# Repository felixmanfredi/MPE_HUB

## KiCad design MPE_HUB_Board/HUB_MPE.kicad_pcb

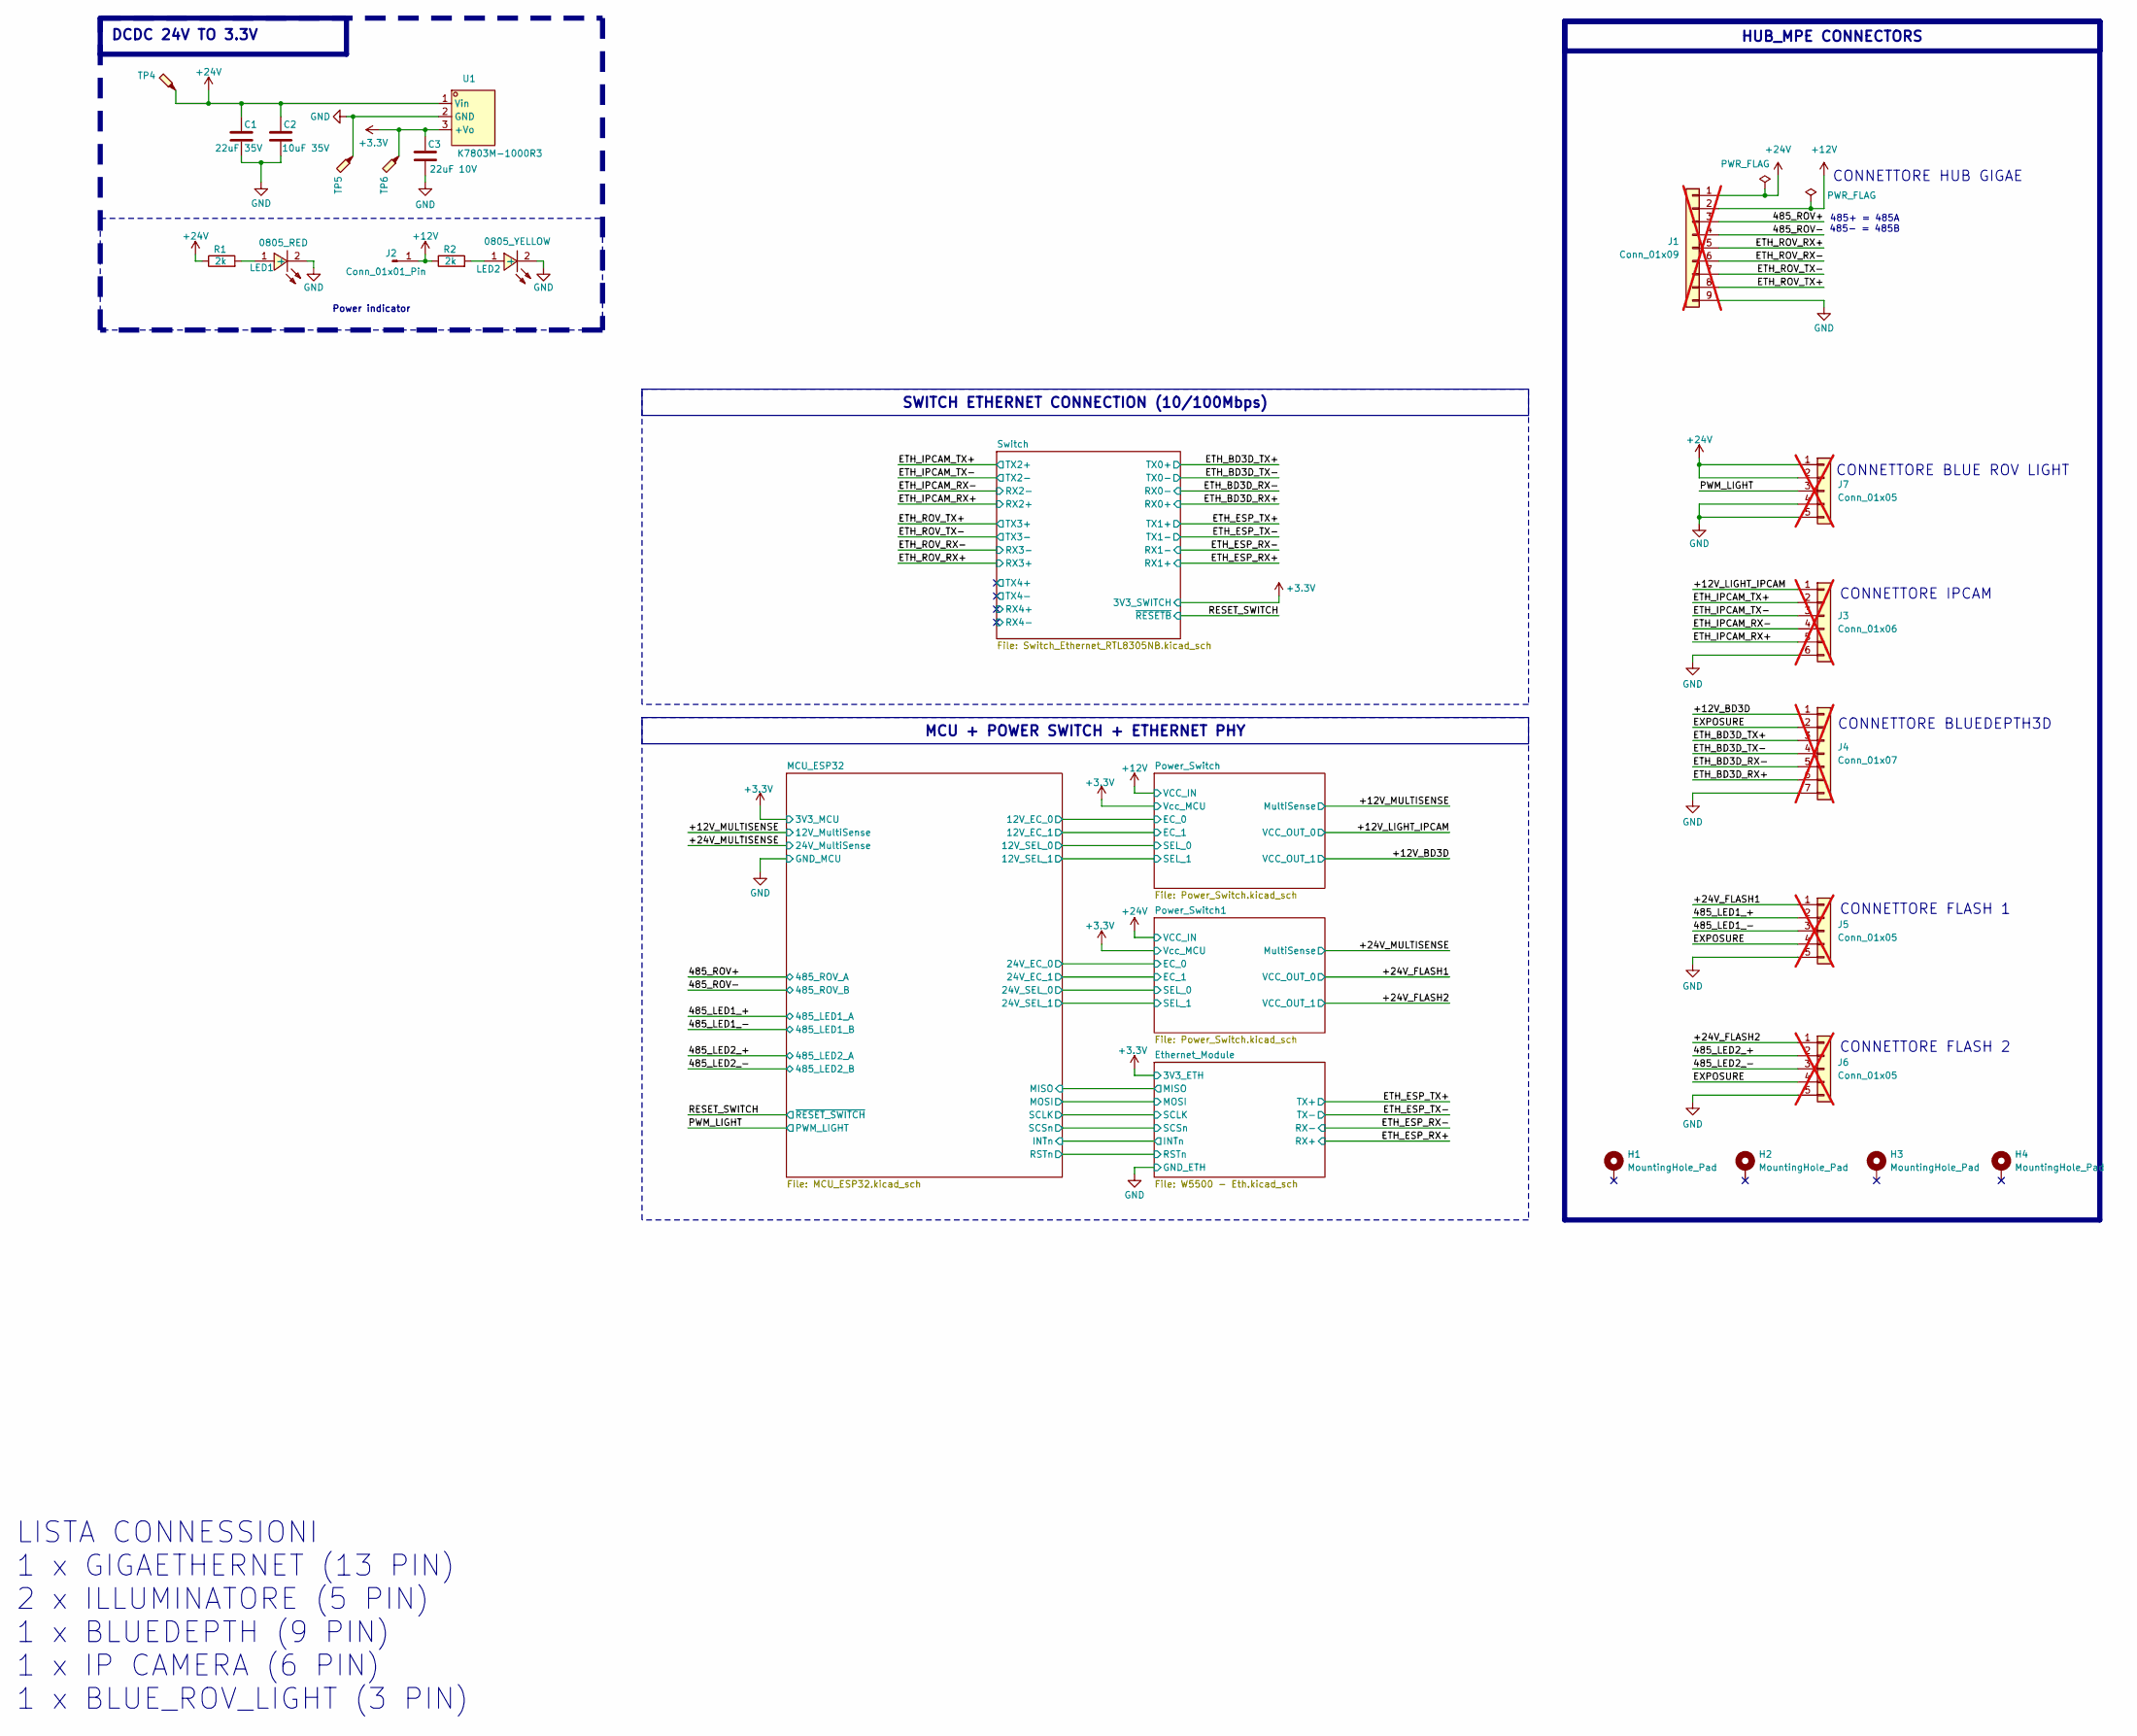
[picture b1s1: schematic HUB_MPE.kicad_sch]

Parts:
C1: 22uF 35V; C_1206_3216Metric; LCSC C342620
C2: 10uF 35V; C_0603_1608Metric; LCSC C194427
C3: 22uF 10V; C_0603_1608Metric; LCSC C60077
H1, H2, H3, H4: MountingHole_Pad; MountingHole_3.2mm_M3_Pad_Via
J1: Conn_01x09; JST_VH_B9P-VH-B_1x09_P3.96mm_Vertical; not fitted
J2: Conn_01x01_Pin; SolderWire-0.75sqmm_1x01_D1.25mm_OD3.5mm
J3: Conn_01x06; JST_VH_B6P-VH-B_1x06_P3.96mm_Vertical; not fitted
J4: Conn_01x07; JST_VH_B7P-VH-B_1x07_P3.96mm_Vertical; not fitted
J5, J6, J7: Conn_01x05; JST_VH_B5P-VH-B_1x05_P3.96mm_Vertical; not fitted
LED1: 0805_RED; LED0805-R-RD; LCSC Part C84256
LED2: 0805_YELLOW; LED0805-R-RD; LCSC Part C2296
R1, R2: 2k; R_0603_1608Metric; LCSC C22975
TP4, TP5, TP6: TestPoint_Probe; TEST-TH_BD2.54-P1.39; LCSC C238122
U1: K7803M-1000R3; PWRM-TH_DEXU_K78XXM-1000R3_XXXXXX; LCSC Part C2916516

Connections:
+3.3V: C3.1, TP6.1, U1.3 (+Vo); also elsewhere on the board
+12V: J1.2, J2.1, R2.1; also elsewhere on the board
+24V: C1.1, C2.1, J1.1, J7.1, J7.2, R1.1, TP4.1, U1.1 (Vin); also elsewhere on the board
/485_LED1_+: J5.2; also elsewhere on the board
/485_LED1_-: J5.3; also elsewhere on the board
/485_LED2_+: J6.2; also elsewhere on the board
/485_LED2_-: J6.3; also elsewhere on the board
/485_ROV+: J1.3; also elsewhere on the board
/485_ROV-: J1.4; also elsewhere on the board
/+12V_BD3D: J4.1; also elsewhere on the board
/+12V_LIGHT_IPCAM: J3.1; also elsewhere on the board
/+24V_FLASH1: J5.1; also elsewhere on the board
/+24V_FLASH2: J6.1; also elsewhere on the board
/ETH_BD3D_RX+: J4.6; also elsewhere on the board
/ETH_BD3D_RX-: J4.5; also elsewhere on the board
/ETH_BD3D_TX+: J4.3; also elsewhere on the board
/ETH_BD3D_TX-: J4.4; also elsewhere on the board
/ETH_IPCAM_RX+: J3.5; also elsewhere on the board
/ETH_IPCAM_RX-: J3.4; also elsewhere on the board
/ETH_IPCAM_TX+: J3.2; also elsewhere on the board
/ETH_IPCAM_TX-: J3.3; also elsewhere on the board
/ETH_ROV_RX+: J1.5; also elsewhere on the board
/ETH_ROV_RX-: J1.6; also elsewhere on the board
/ETH_ROV_TX+: J1.8; also elsewhere on the board
/ETH_ROV_TX-: J1.7; also elsewhere on the board
/EXPOSURE: J4.2, J5.4, J6.4
/PWM_LIGHT: J7.3; also elsewhere on the board
unnamed: LED1.1 (+), R1.2
unnamed: LED2.1 (+), R2.2

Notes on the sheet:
CONNETTORE FLASH 1
Power indicator
CONNETTORE HUB GIGAE
CONNETTORE IPCAM
485+ = 485A 485- = 485B
LISTA CONNESSIONI 1 x GIGAETHERNET (13 PIN) 2 x ILLUMINATORE (5 PIN) 1 x BLUEDEPTH (9 PIN) 1 x IP CAMERA (6 PIN) 1 x BLUE_ROV_LIGHT (3 PIN)
CONNETTORE BLUEDEPTH3D
CONNETTORE BLUE ROV LIGHT
CONNETTORE FLASH 2
MCU + POWER SWITCH + ETHERNET PHY
HUB_MPE CONNECTORS
SWITCH ETHERNET CONNECTION (10/100Mbps)
DCDC 24V TO 3.3V

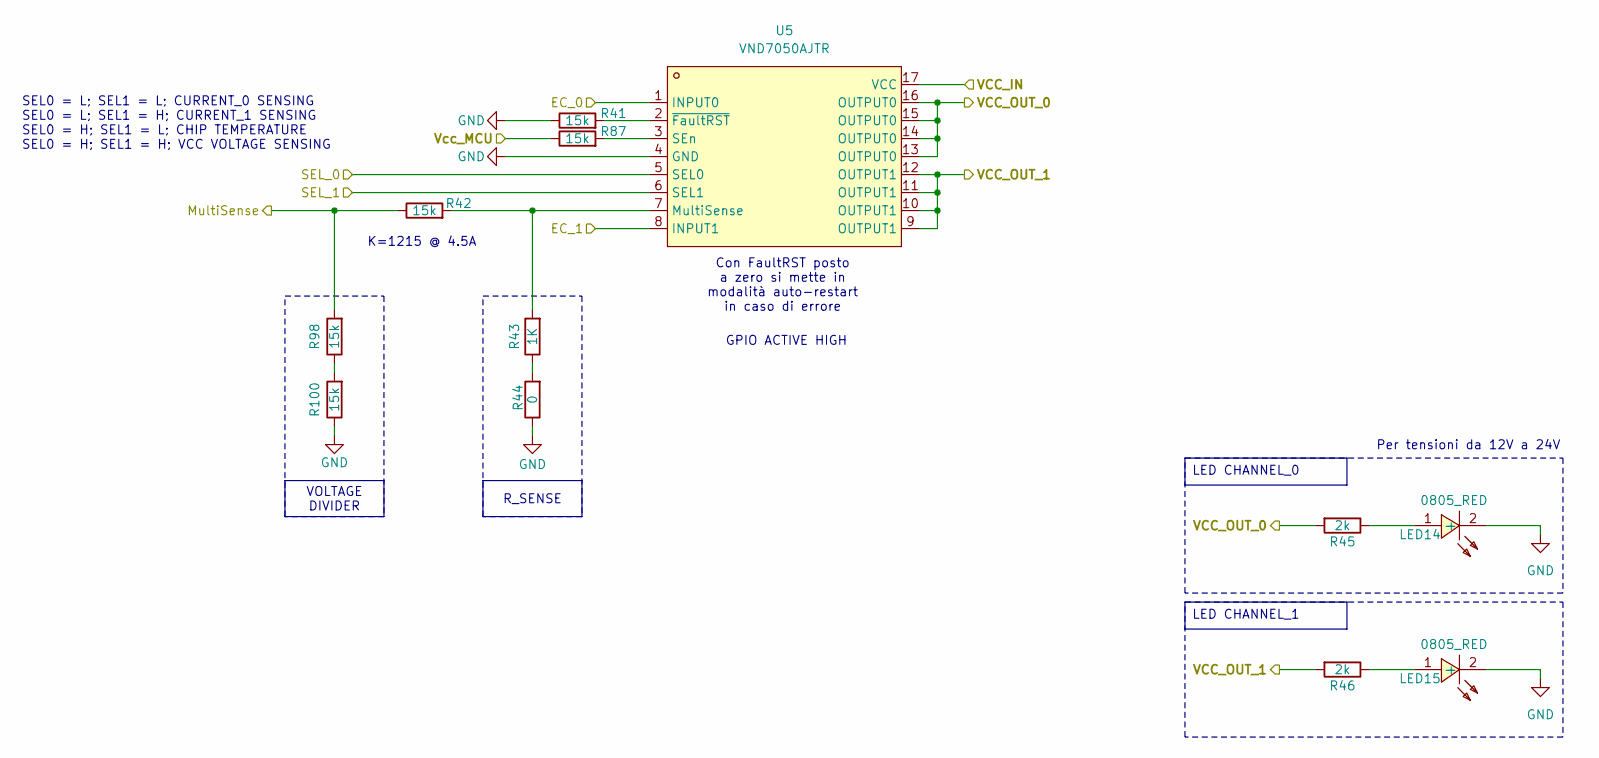
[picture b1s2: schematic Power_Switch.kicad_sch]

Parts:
LED14, LED15: 0805_RED; LED0805-R-RD; LCSC Part C84256
R41, R42, R87, R98, R100: 15k; R_0603_1608Metric; LCSC C22809
R43: 1K; R_0603_1608Metric; LCSC Part C21190
R44: 0; R_0603_1608Metric; LCSC C21189
R45, R46: 2k; R_0603_1608Metric; LCSC C22975
U5: VND7050AJTR; POWERSSO-16_L4.9-W3.9-P0.50-LS6.0-BL-EP; LCSC Part C443997

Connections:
+3.3V: R87.1; also elsewhere on the board
+12V: U5.17 (VCC); also elsewhere on the board
/+12V_BD3D: R46.2, U5.9 (OUTPUT1), U5.10 (OUTPUT1), U5.11 (OUTPUT1), U5.12 (OUTPUT1); also elsewhere on the board
/+12V_LIGHT_IPCAM: R45.2, U5.13 (OUTPUT0), U5.14 (OUTPUT0), U5.15 (OUTPUT0), U5.16 (OUTPUT0); also elsewhere on the board
/+12V_MULTISENSE: R42.1, R98.2; also elsewhere on the board
/MCU_ESP32/12V_EC_0: U5.1 (INPUT0); also elsewhere on the board
/MCU_ESP32/12V_EC_1: U5.8 (INPUT1); also elsewhere on the board
/MCU_ESP32/12V_SEL_0: U5.5 (SEL0); also elsewhere on the board
/MCU_ESP32/12V_SEL_1: U5.6 (SEL1); also elsewhere on the board
unnamed: LED14.1 (+), R45.1
unnamed: LED15.1 (+), R46.1
unnamed: R43.1, R44.2
unnamed: R98.1, R100.2
unnamed: R42.2, R43.2, U5.7 (MultiSense)
unnamed: R87.2, U5.3 (SEn)
unnamed: R41.2, U5.2 (~FaultRST)

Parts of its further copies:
LED16, LED17: 0805_RED; LED0805-R-RD; LCSC Part C84256
R47, R48, R88, R99, R101: 15k; R_0603_1608Metric; LCSC C22809
R49: 1K; R_0603_1608Metric; LCSC Part C21190
R50: 0; R_0603_1608Metric; LCSC C21189
R51, R52: 2k; R_0603_1608Metric; LCSC C22975
U6: VND7050AJTR; POWERSSO-16_L4.9-W3.9-P0.50-LS6.0-BL-EP; LCSC Part C443997

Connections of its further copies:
+3.3V: R88.1; also elsewhere on the board
+24V: U6.17 (VCC); also elsewhere on the board
/+24V_FLASH1: R51.2, U6.13 (OUTPUT0), U6.14 (OUTPUT0), U6.15 (OUTPUT0), U6.16 (OUTPUT0); also elsewhere on the board
/+24V_FLASH2: R52.2, U6.9 (OUTPUT1), U6.10 (OUTPUT1), U6.11 (OUTPUT1), U6.12 (OUTPUT1); also elsewhere on the board
/+24V_MULTISENSE: R48.1, R99.2; also elsewhere on the board
/MCU_ESP32/24V_EC_0: U6.1 (INPUT0); also elsewhere on the board
/MCU_ESP32/24V_EC_1: U6.8 (INPUT1); also elsewhere on the board
/MCU_ESP32/24V_SEL_0: U6.5 (SEL0); also elsewhere on the board
/MCU_ESP32/24V_SEL_1: U6.6 (SEL1); also elsewhere on the board
unnamed: LED16.1 (+), R51.1
unnamed: LED17.1 (+), R52.1
unnamed: R49.1, R50.2
unnamed: R99.1, R101.2
unnamed: R48.2, R49.2, U6.7 (MultiSense)
unnamed: R88.2, U6.3 (SEn)
unnamed: R47.2, U6.2 (~FaultRST)

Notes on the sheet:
K=1215 @ 4.5A
Per tensioni da 12V a 24V
GPIO ACTIVE HIGH
SEL0 = L; SEL1 = L; CURRENT_0 SENSING SEL0 = L; SEL1 = H; CURRENT_1 SENSING SEL0 = H; SEL1 = L; CHIP TEMPERATURE SEL0 = H; SEL1 = H; VCC VOLTAGE SENSING
Con FaultRST posto a zero si mette in modalità auto-restart in caso di errore
R_SENSE
VOLTAGE DIVIDER
LED CHANNEL_1
LED CHANNEL_0

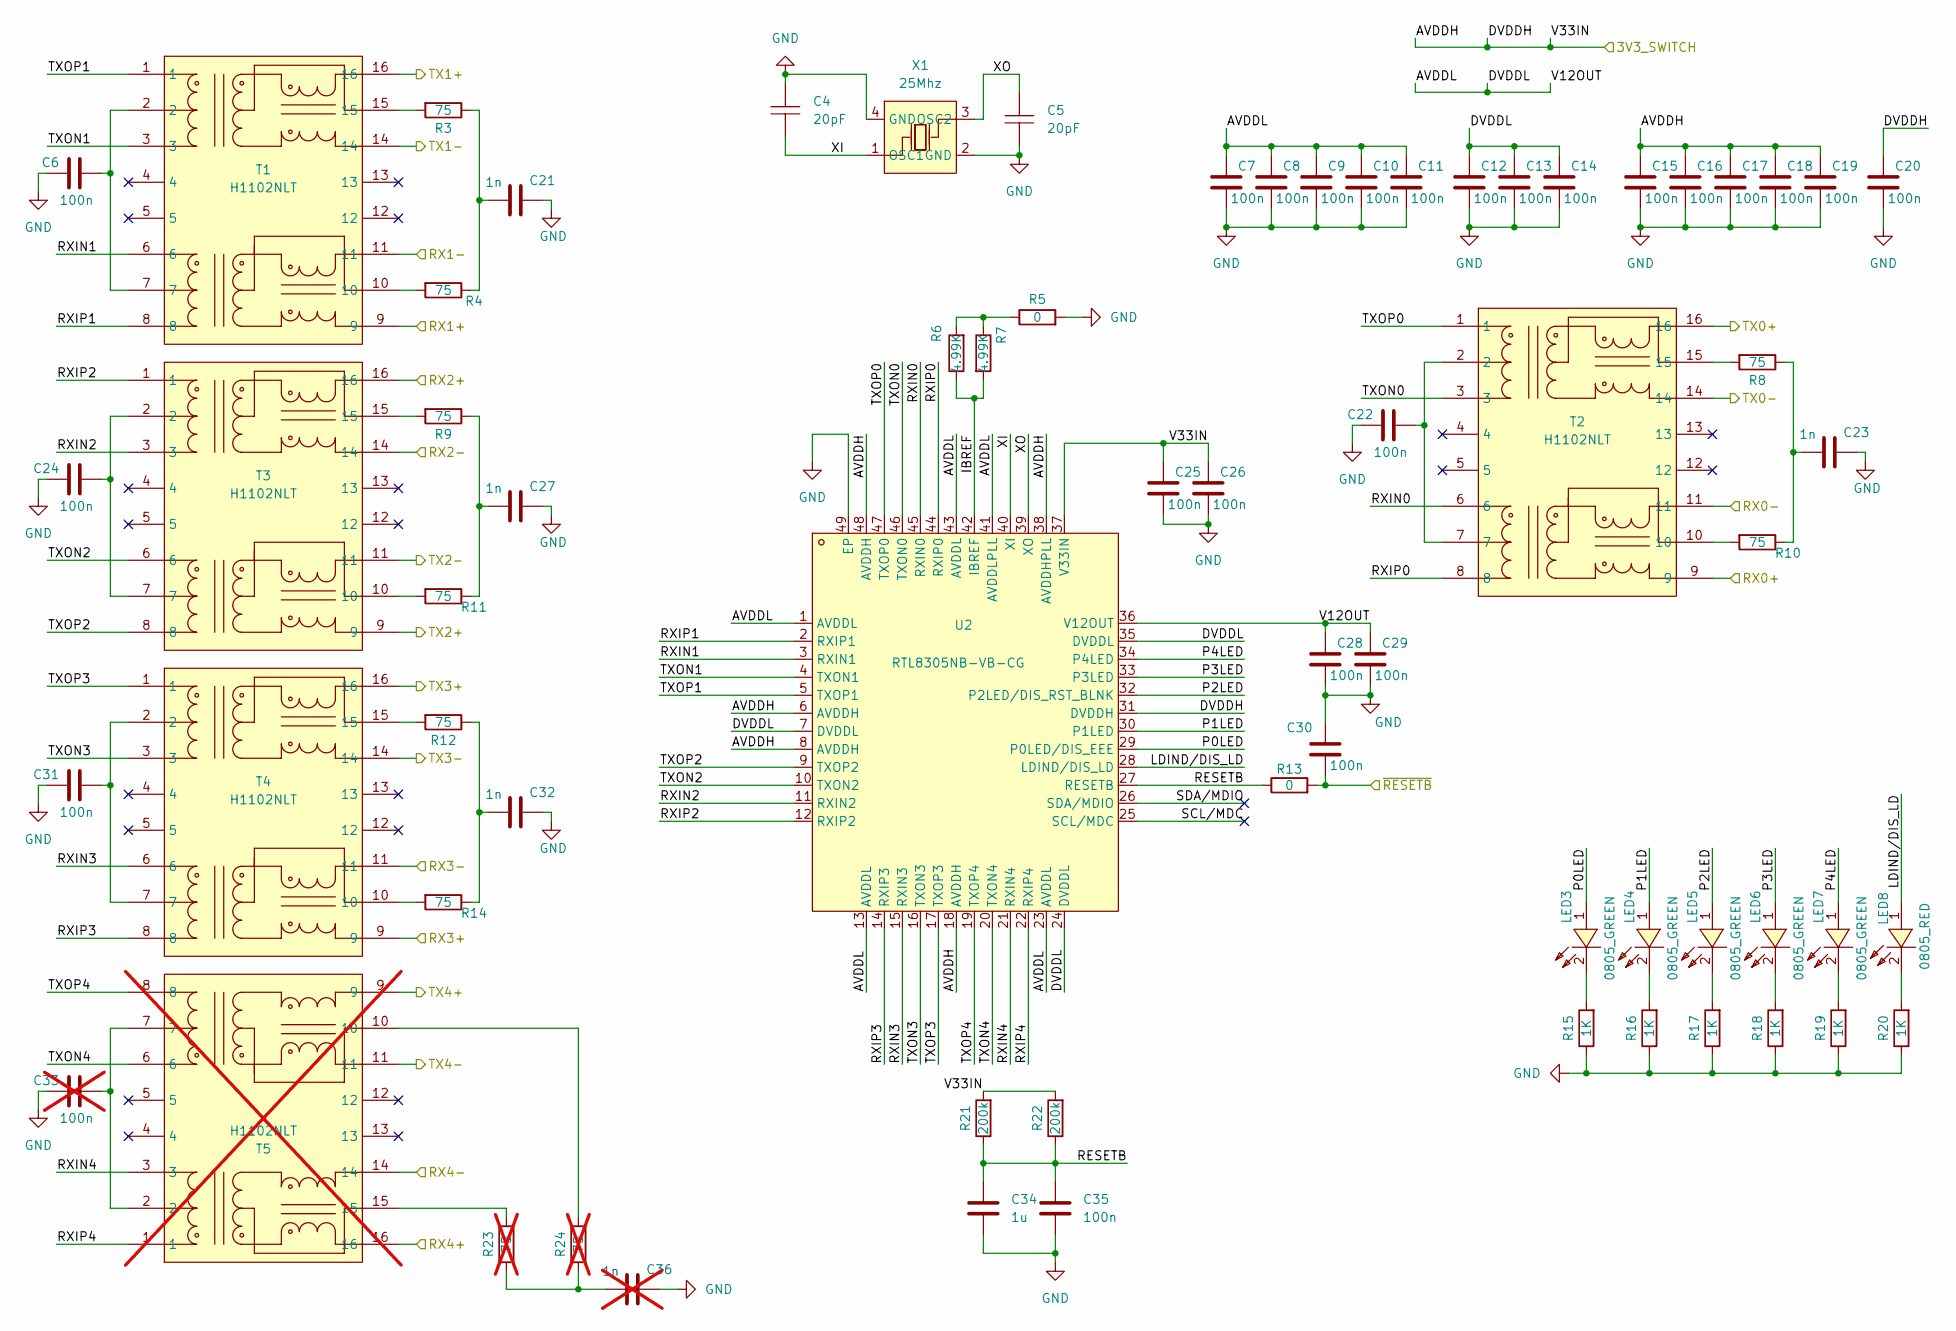
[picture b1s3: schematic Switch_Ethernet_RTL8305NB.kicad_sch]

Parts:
C4, C5: 20pF; C_0603_1608Metric; LCSC Part C1648
C6, C7, C8, C9, C10, C11, C12, C13, C14, C15, C16, C17, C18, C19, C20, C22, C24, C25, C26, C28, C29, C30, C31, C35: 100n; C_0603_1608Metric; LCSC Part C14663
C21, C23, C27, C32: 1n; C_0603_1608Metric; LCSC Part C1588
C33: 100n; C_0603_1608Metric; LCSC Part C14663; not fitted
C34: 1u; C_0603_1608Metric; LCSC Part C15849
C36: 1n; C_0603_1608Metric; LCSC Part C1588; not fitted
LED3, LED4, LED5, LED6, LED7: 0805_GREEN; LED0805-R-RD; LCSC Part C2297
LED8: 0805_RED; LED0805-R-RD; LCSC Part C84256
R3, R4, R8, R9, R10, R11, R12, R14: 75; R_0603_1608Metric; LCSC Part C4275
R5, R13: 0; R_0603_1608Metric; LCSC Part C21189
R6, R7: 4.99K; R_0603_1608Metric; LCSC Part C23046
R15, R16, R17, R18, R19, R20: 1K; R_0603_1608Metric; LCSC Part C21190
R21, R22: 200k; R_0603_1608Metric; LCSC Part C25811
R23, R24: 75; R_0603_1608Metric; LCSC Part C4275; not fitted
T1, T2, T3, T4: H1102NLT; XFMR-SMD_H1102NLT; LCSC Part C18584
T5: H1102NLT; XFMR-SMD_H1102NLT; LCSC Part C18584; not fitted
U2: RTL8305NB-VB-CG; QFN-48_L6.0-W6.0-P0.40-TL-EP4.4; LCSC Part C3010343
X1: 25Mhz; CRYSTAL-SMD_4P-L3.2-W2.5-BL; LCSC Part C9006

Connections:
+3.3V: C15.1, C16.1, C17.1, C18.1, C19.1, C20.1, C25.1, C26.1, R21.2, R22.2, U2.6 (AVDDH), U2.8 (AVDDH), U2.18 (AVDDH), U2.31 (DVDDH), U2.37 (V33IN), U2.38 (AVDDHPLL), U2.48 (AVDDH); also elsewhere on the board
/ETH_BD3D_RX+: T2.9; also elsewhere on the board
/ETH_BD3D_RX-: T2.11; also elsewhere on the board
/ETH_BD3D_TX+: T2.16; also elsewhere on the board
/ETH_BD3D_TX-: T2.14; also elsewhere on the board
/ETH_ESP_RX+: T1.9; also elsewhere on the board
/ETH_ESP_RX-: T1.11; also elsewhere on the board
/ETH_ESP_TX+: T1.16; also elsewhere on the board
/ETH_ESP_TX-: T1.14; also elsewhere on the board
/ETH_IPCAM_RX+: T3.16; also elsewhere on the board
/ETH_IPCAM_RX-: T3.14; also elsewhere on the board
/ETH_IPCAM_TX+: T3.9; also elsewhere on the board
/ETH_IPCAM_TX-: T3.11; also elsewhere on the board
/ETH_ROV_RX+: T4.9; also elsewhere on the board
/ETH_ROV_RX-: T4.11; also elsewhere on the board
/ETH_ROV_TX+: T4.16; also elsewhere on the board
/ETH_ROV_TX-: T4.14; also elsewhere on the board
/RESET_SWITCH: C30.2, R13.2; also elsewhere on the board
/Switch/LDIND/DIS_LD: LED8.1 (+), U2.28 (LDIND/DIS_LD)
/Switch/P0LED: LED3.1 (A), U2.29 (P0LED/DIS_EEE)
/Switch/P1LED: LED4.1 (A), U2.30 (P1LED)
/Switch/P2LED: LED5.1 (A), U2.32 (P2LED/DIS_RST_BLNK)
/Switch/P3LED: LED6.1 (A), U2.33 (P3LED)
/Switch/P4LED: LED7.1 (A), U2.34 (P4LED)
/Switch/RESETB: C34.1, C35.1, R13.1, R21.1, R22.1, U2.27 (RESETB)
/Switch/RXIN0: T2.6, U2.45 (RXIN0)
/Switch/RXIN1: T1.6, U2.3 (RXIN1)
/Switch/RXIN2: T3.3, U2.11 (RXIN2)
/Switch/RXIP0: T2.8, U2.44 (RXIP0)
/Switch/RXIP1: T1.8, U2.2 (RXIP1)
/Switch/RXIP2: T3.1, U2.12 (RXIP2)
/Switch/SCL/MDC: U2.25 (SCL/MDC)
/Switch/SDA/MDIO: U2.26 (SDA/MDIO)
/Switch/TXON0: T2.3, U2.46 (TXON0)
/Switch/TXON1: T1.3, U2.4 (TXON1)
/Switch/TXON2: T3.6, U2.10 (TXON2)
/Switch/TXOP0: T2.1, U2.47 (TXOP0)
/Switch/TXOP1: T1.1, U2.5 (TXOP1)
/Switch/TXOP2: T3.8, U2.9 (TXOP2)
/Switch/XI: C4.1, U2.40 (XI), X1.1 (OSC1)
unnamed: C6.1, T1.2, T1.7
unnamed: C21.2, R3.1, R4.1
unnamed: C22.1, T2.2, T2.7
unnamed: C24.1, T3.2, T3.7
unnamed: C27.2, R9.1, R11.1
unnamed: C32.2, R12.1, R14.1
unnamed: LED3.2 (K), R15.2
unnamed: LED4.2 (K), R16.2
unnamed: LED5.2 (K), R17.2
unnamed: LED6.2 (K), R18.2
unnamed: LED7.2 (K), R19.2
unnamed: LED8.2 (-), R20.2
unnamed: R3.2, T1.15
unnamed: R4.2, T1.10
unnamed: R8.2, T2.15
unnamed: R9.2, T3.15
unnamed: R11.2, T3.10

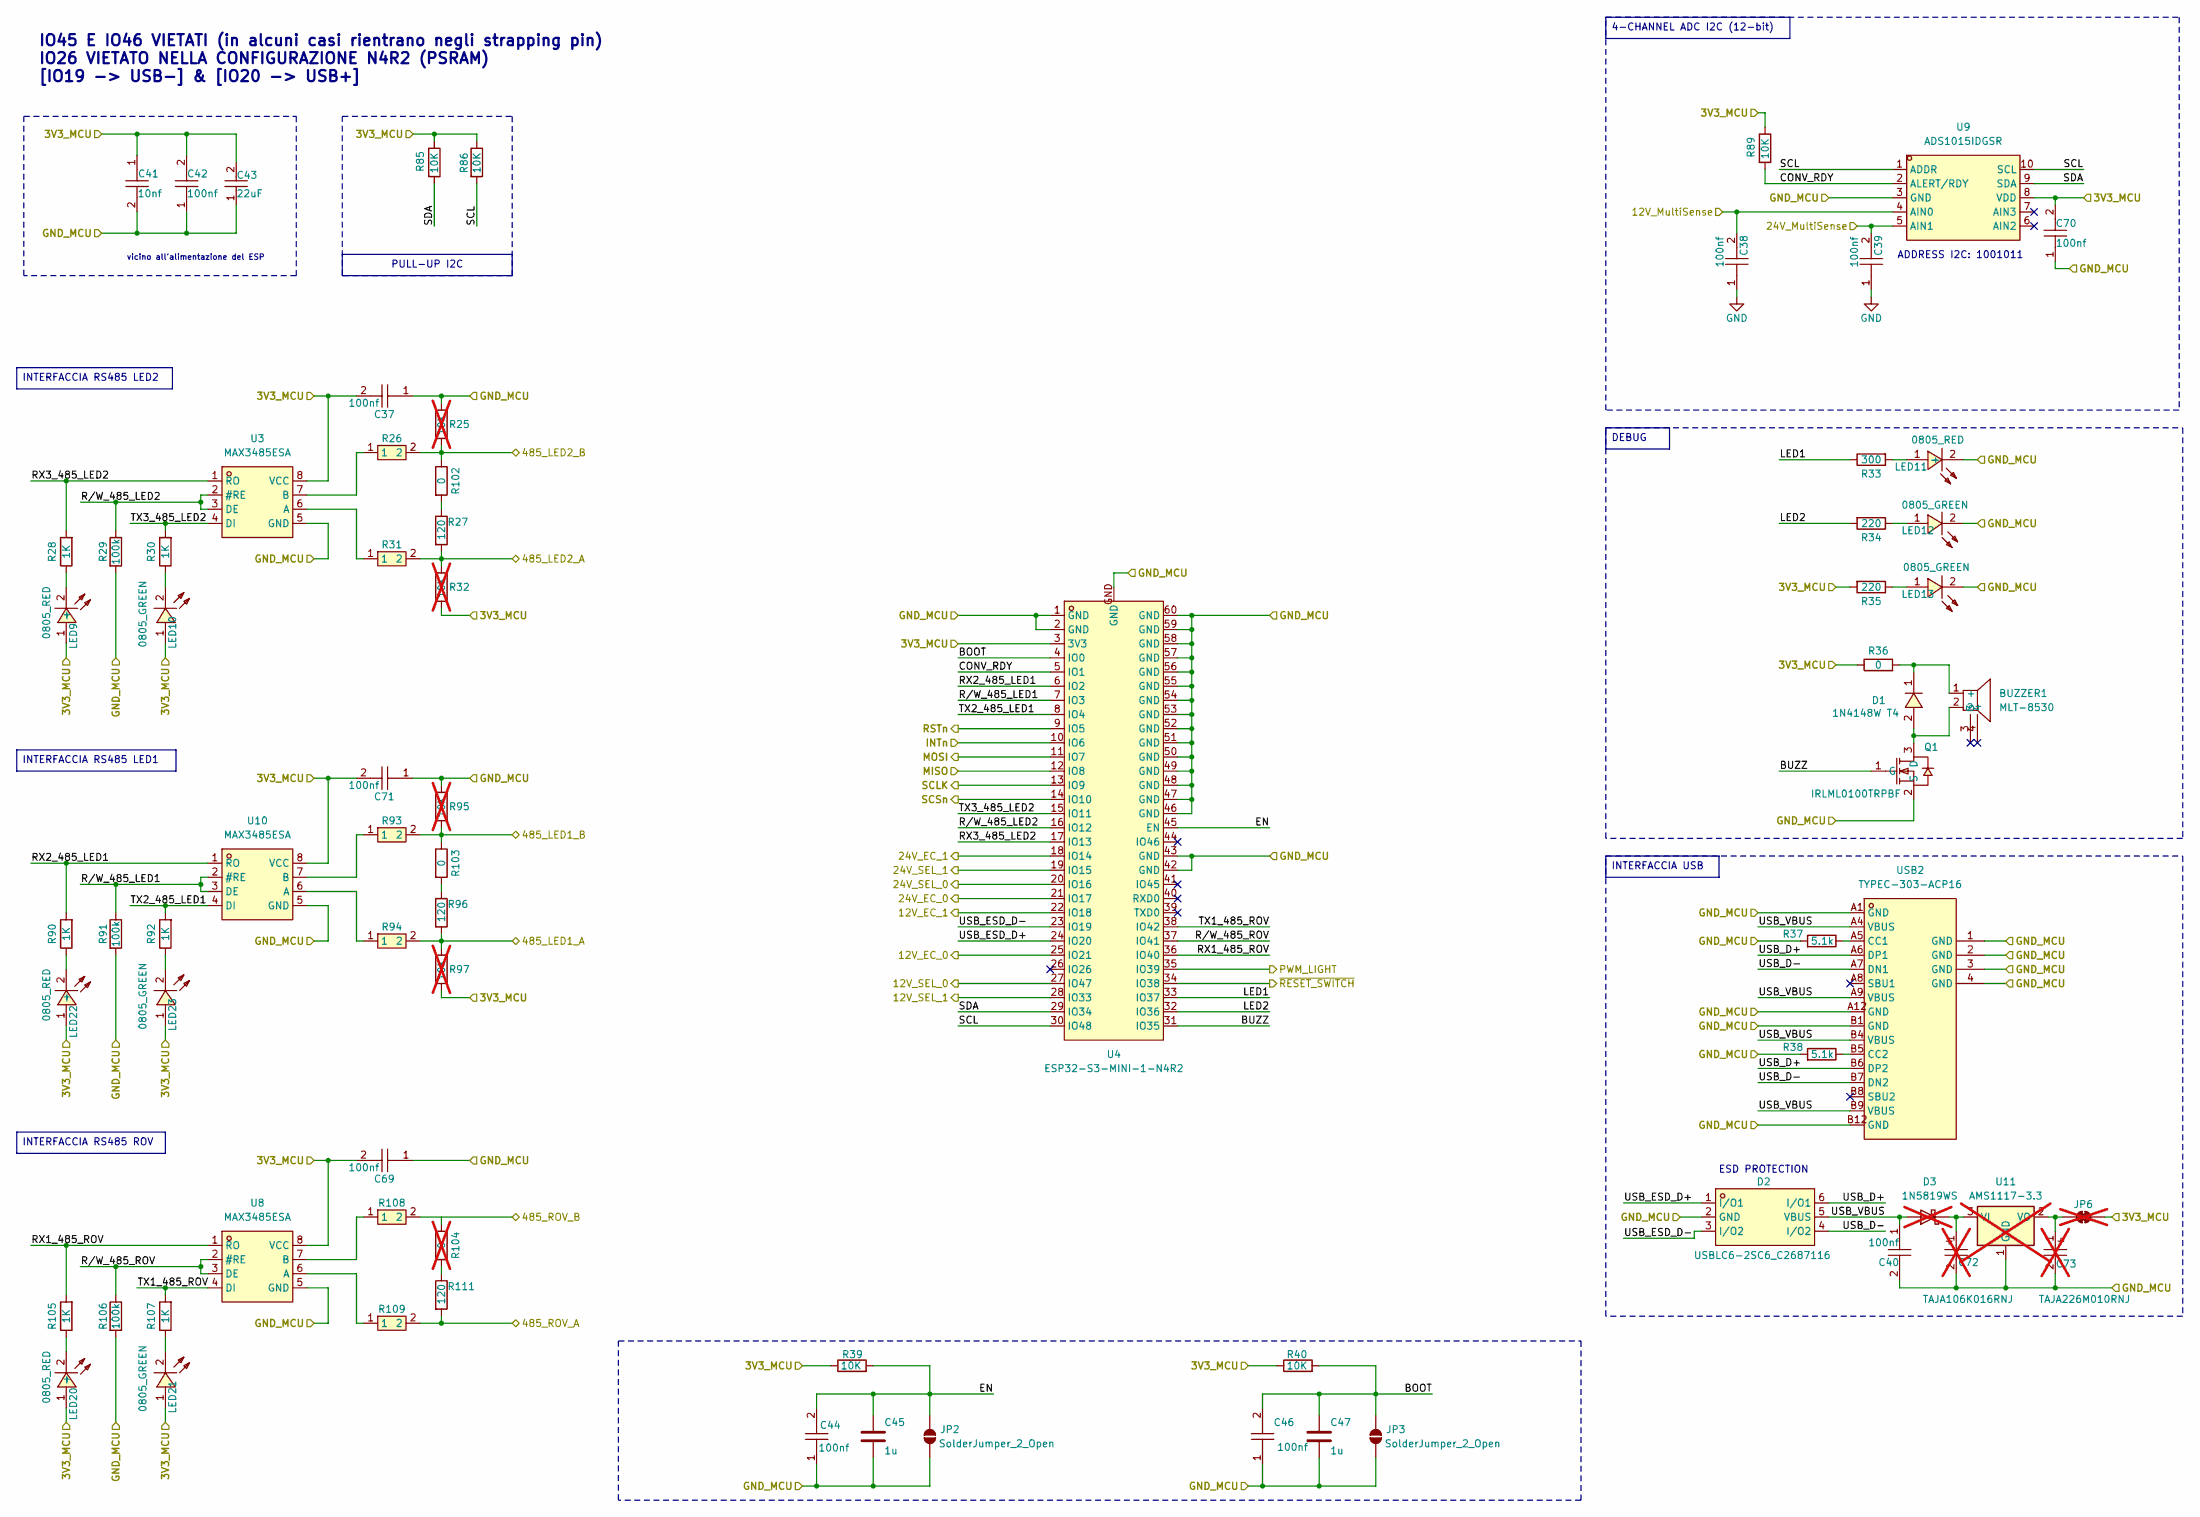
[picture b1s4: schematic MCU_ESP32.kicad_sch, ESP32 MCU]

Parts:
BUZZER1: MLT-8530; BUZ-SMD_4P-L8.5-W8.5-P8.50-BR; LCSC Part C94599
C37, C38, C39, C40, C42, C44, C46, C69, C70, C71: 100nf; C_0603_1608Metric; LCSC Part C14663
C41: 10nf; C_0603_1608Metric; LCSC Part C57112
C43: 22uF; C_0603_1608Metric; LCSC Part C12891
C45, C47: 1u; C_0603_1608Metric; LCSC part C15849
C72: TAJA106K016RNJ; CAP-SMD_L3.2-W1.6-RD-C7171; LCSC Part C7171; not fitted
C73: TAJA226M010RNJ; CASE-A_3216; LCSC Part C7183; not fitted
D1: 1N4148W T4; SOD-123_L2.8-W1.8-LS3.7-RD; LCSC Part C2099
D2: USBLC6-2SC6_C2687116; SOT-23-6_L2.9-W1.6-P0.95-LS2.8-BL; LCSC Part C2687116
D3: 1N5819WS; D_SOD-323; not fitted
JP2, JP3: SolderJumper_2_Open; SolderJumper-2_P1.3mm_Open_RoundedPad1.0x1.5mm
JP6: SolderJumper_2_Bridged; SolderJumper-2_P1.3mm_Bridged_RoundedPad1.0x1.5mm; not fitted
LED9, LED11, LED20, LED22: 0805_RED; LED0805-R-RD; LCSC Part C84256
LED10, LED12, LED13, LED21, LED23: 0805_GREEN; LED0805-R-RD; LCSC Part C2297
Q1: IRLML0100TRPBF; SOT-23_L2.9-W1.3-P1.90-LS2.4-BR; LCSC Part C53658
R25, R32, R95, R97: 10K; R_0603_1608Metric; LCSC Part C25804; not fitted
R26, R31, R93, R94, R108, R109: CRCW060310R0JNEAHP; R0603; LCSC Part C844519
R27, R96, R111: 120; R_0603_1608Metric; LCSC C22787
R28, R30, R90, R92, R105, R107: 1K; R_0603_1608Metric; LCSC Part C21190
R29, R91, R106: 100k; R_0603_1608Metric; LCSC Part C25803
R33: 300; R_0603_1608Metric; LCSC Part C23025
R34, R35: 220; R_0603_1608Metric; LCSC Part C22962
R36, R102, R103: 0; R_0603_1608Metric; LCSC C21189
R37, R38: 5.1k; R_0603_1608Metric
R39, R40, R85, R86, R89: 10K; R_0603_1608Metric; LCSC Part C25804
R104: 0; R_0603_1608Metric; LCSC C21189; not fitted
U3, U8, U10: MAX3485ESA; SOP-8_L5.0-W4.0-P1.27-LS6.0-BL; LCSC Part C668204
U4: ESP32-S3-MINI-1-N4R2; BULETM-SMD_ESP32-S3-MINI-1-N8; LCSC Part C3013941
U9: ADS1015IDGSR; VSSOP-10_L3.0-W3.0-P0.50-LS4.9-BL; LCSC Part C193969
U11: AMS1117-3.3; SOT-223-3_TabPin2; not fitted
USB2: TYPEC-303-ACP16; USB-C-SMD_TYPEC-303-ACP16; LCSC Part C720628

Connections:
+3.3V: C37.2, C41.1, C42.2, C43.2, C69.2, C70.2, C71.2, JP6.2 (B), LED9.1 (+), LED10.1 (A), LED20.1 (+), LED21.1 (A), LED22.1 (+), LED23.1 (A), R32.2, R35.2, R36.1, R39.1, R40.1, R85.1, R86.1, R89.1, R97.2, U3.8 (VCC), U4.3 (3V3), U8.8 (VCC), U9.8 (VDD), U10.8 (VCC); also elsewhere on the board
/485_LED1_+: R94.2, R96.2, R97.1; also elsewhere on the board
/485_LED1_-: R93.2, R95.2, R103.1; also elsewhere on the board
/485_LED2_+: R27.2, R31.2, R32.1; also elsewhere on the board
/485_LED2_-: R25.2, R26.2, R102.1; also elsewhere on the board
/485_ROV+: R109.2, R111.2; also elsewhere on the board
/485_ROV-: R108.2; also elsewhere on the board
/+12V_MULTISENSE: C38.2, U9.4 (AIN0); also elsewhere on the board
/+24V_MULTISENSE: C39.2, U9.5 (AIN1); also elsewhere on the board
/Ethernet_Module/MISO: U4.12 (IO8); also elsewhere on the board
/Ethernet_Module/MOSI: U4.11 (IO7); also elsewhere on the board
/Ethernet_Module/RSTn: U4.9 (IO5); also elsewhere on the board
/Ethernet_Module/SCLK: U4.13 (IO9); also elsewhere on the board
/Ethernet_Module//INT: U4.10 (IO6); also elsewhere on the board
/Ethernet_Module//SPI-SCS: U4.14 (IO10); also elsewhere on the board
/MCU_ESP32/12V_EC_0: U4.25 (IO21); also elsewhere on the board
/MCU_ESP32/12V_EC_1: U4.22 (IO18); also elsewhere on the board
/MCU_ESP32/12V_SEL_0: U4.27 (IO47); also elsewhere on the board
/MCU_ESP32/12V_SEL_1: U4.28 (IO33); also elsewhere on the board
/MCU_ESP32/24V_EC_0: U4.21 (IO17); also elsewhere on the board
/MCU_ESP32/24V_EC_1: U4.18 (IO14); also elsewhere on the board
/MCU_ESP32/24V_SEL_0: U4.20 (IO16); also elsewhere on the board
/MCU_ESP32/24V_SEL_1: U4.19 (IO15); also elsewhere on the board
/MCU_ESP32/BOOT: C46.2, C47.1, JP3.2 (B), R40.2, U4.4 (IO0)
/MCU_ESP32/BUZZ: Q1.1 (G), U4.31 (IO35)
/MCU_ESP32/CONV_RDY: R89.2, U4.5 (IO1), U9.2 (ALERT/RDY)
/MCU_ESP32/EN: C44.2, C45.1, JP2.2 (B), R39.2, U4.45 (EN)
/MCU_ESP32/LED1: R33.1, U4.33 (IO37)
/MCU_ESP32/LED2: R34.2, U4.32 (IO36)
/MCU_ESP32/RX1_485_ROV: R105.2, U4.36 (IO40), U8.1 (RO)
/MCU_ESP32/RX2_485_LED1: R90.2, U4.6 (IO2), U10.1 (RO)
/MCU_ESP32/RX3_485_LED2: R28.2, U3.1 (RO), U4.17 (IO13)
/MCU_ESP32/R/W_485_LED1: R91.1, U4.7 (IO3), U10.2 (#RE), U10.3 (DE)
/MCU_ESP32/R/W_485_LED2: R29.1, U3.2 (#RE), U3.3 (DE), U4.16 (IO12)
/MCU_ESP32/R/W_485_ROV: R106.1, U4.37 (IO41), U8.2 (#RE), U8.3 (DE)
/MCU_ESP32/SCL: R86.2, U4.30 (IO48), U9.1 (ADDR), U9.10 (SCL)
/MCU_ESP32/SDA: R85.2, U4.29 (IO34), U9.9 (SDA)
/MCU_ESP32/TX1_485_ROV: R107.2, U4.38 (IO42), U8.4 (DI)
/MCU_ESP32/TX2_485_LED1: R92.2, U4.8 (IO4), U10.4 (DI)
/MCU_ESP32/TX3_485_LED2: R30.2, U3.4 (DI), U4.15 (IO11)
/MCU_ESP32/USB_D+: D2.6 (I/O1), USB2.A6 (DP1), USB2.B6 (DP2)
/MCU_ESP32/USB_D-: D2.4 (I/O2), USB2.A7 (DN1), USB2.B7 (DN2)
/MCU_ESP32/USB_ESD_D+: D2.1 (I/O1), U4.24 (IO20)
/MCU_ESP32/USB_ESD_D-: D2.3 (I/O2), U4.23 (IO19)
/MCU_ESP32/USB_VBUS: C40.1, D2.5 (VBUS), D3.2 (A), USB2.A4 (VBUS), USB2.A9 (VBUS), USB2.B4 (VBUS), USB2.B9 (VBUS)
/PWM_LIGHT: U4.35 (IO39); also elsewhere on the board
/RESET_SWITCH: U4.34 (IO38); also elsewhere on the board
unnamed: BUZZER1.1 (+), D1.1 (K), R36.2
unnamed: C72.1, D3.1 (K), U11.3 (VI)
unnamed: C73.1, JP6.1 (A), U11.2 (VO)
unnamed: BUZZER1.2, D1.2 (A), Q1.3 (D)
unnamed: LED9.2 (-), R28.1
unnamed: LED10.2 (K), R30.1
unnamed: LED11.1 (+), R33.2
unnamed: LED12.1 (A), R34.1
unnamed: LED13.1 (A), R35.1
unnamed: LED20.2 (-), R105.1
unnamed: LED21.2 (K), R107.1
unnamed: LED22.2 (-), R90.1
unnamed: LED23.2 (K), R92.1
unnamed: R27.1, R102.2
unnamed: R96.1, R103.2
unnamed: R104.2, R111.1
unnamed: R31.1, U3.6 (A)
unnamed: R26.1, U3.7 (B)
unnamed: R109.1, U8.6 (A)
unnamed: R108.1, U8.7 (B)
unnamed: R94.1, U10.6 (A)
unnamed: R93.1, U10.7 (B)
unnamed: R37.1, USB2.A5 (CC1)
unnamed: R38.1, USB2.B5 (CC2)

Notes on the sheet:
ESD PROTECTION
vicino all'alimentazione del ESP
IO45 E IO46 VIETATI (in alcuni casi rientrano negli strapping pin) IO26 VIETATO NELLA CONFIGURAZIONE N4R2 (PSRAM) [IO19 -> USB-] & [IO20 -> USB+]
ADDRESS I2C: 1001011
INTERFACCIA RS485 ROV
4-CHANNEL ADC I2C (12-bit)
DEBUG
INTERFACCIA RS485 LED2
PULL-UP I2C
INTERFACCIA RS485 LED1
INTERFACCIA USB
